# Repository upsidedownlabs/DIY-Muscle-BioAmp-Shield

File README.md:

# Muscle BioAmp Shield

[-white)](https://store.upsidedownlabs.tech/product/muscle-bioamp-shield-v0-3/)

Muscle BioAmp Shield is an all-in-one Arduino Uno ElectroMyography (EMG) shield for learning neuroscience with ease. It is a DIY Electrophysiology/NeuroScience shield inspired from Back Yard Brains (BYB) Muscle Spiker shield and provides similar features like hobby servo output, user buttons, LED Bar, Audio output, and battery input. It is perfect for beginners as they can easily stack it on top of Arduino Uno to record, visualize and listen to their muscle signals to make amazing projects in the domain of Human-Computer Interface (HCI).

## Features & Specifications

Muscle BioAmp Shield comes with various plug-and-play options so you can connect hundreds of extension boards like OLED screens, character displays, accelerometers, and servo controllers to name just a few using the STEMMA I2C interface. You also get STEMMA digital and STEMMA analog ports. On STEMMA analog port you can connect additional [BioAmp EXG Pill](https://github.com/upsidedownlabs/BioAmp-EXG-Pill) or any other sensor with analog output. On STEMMA digital port you can connect any digital sensor or actuator of your choice.

## Assembly
You can get your own Muscle BioAmp Shield bag of parts from [our store](https://store.upsidedownlabs.tech/product/muscle-bioamp-shield-v0-3/) or [Tindie](www.tindie.com/products/upsidedownlabs/muscle-bioamp-shield-v03-arduino-shield-for-emg/) and for assembling your shield you can take a look at [this interactive BOM](https://upsidedownlabs.github.io/DIY-Muscle-BioAmp-Shield/ibom.html) or the step by step guide below. 

| Step 1 - Bare board | Step 2 - 1M Resistors | Step 3 - 330R Resistors| 
| :----: | :----: | :----: |
| |||

| Step 4 - 10K Resistors | Step 5 - 22K Resistors | Step 6 - 1K Resistors| 
| :----: | :----: | :----: |
| |||

| Step 7 - 220K Resistors | Step 8 - 1nF Capacitors | Step 9 - 100nF Capacitors| 
| :----: | :----: | :----: |
| |||

| Step 10 - 100pF Capacitors | Step 11 - Servo Header Pin | Step 12 - Buttons| 
| :----: | :----: | :----: |
| |||

| Step 13 - Optoisolator | Step 14 - Angled JST Connectors | Step 15 - Straight JST Connectors| 
| :----: | :----: | :----: |
| |||

| Step 16 - IC Socket | Step 17 - IC | Step 18 - LEDs| 
| :----: | :----: | :----: |
| |||

| Step 19 - 3.5mm Headphone Jack | Step 20 - 2.2uF Capacitor | Step 21 - 1uF Capacitor| 
| :----: | :----: | :----: |
| |||

| Step 22 - 470uF Capacitors | Step 23 - Shield Header Pins | Step 24 - Shield Ready| 
| :----: | :----: | :----: |
| |||

## What's in the kit

Muscle BioAmp Shield comes in two variants: Pre-Assembled and DIY (Do-It-Yourself). You can order any of the two variants as per your requirement.

## Hardware

Muscle BioAmp Shield has been created using KiCad and all the design files can be found under [hardware](hardware/) folder, including [Interactive BOM](https://upsidedownlabs.github.io/DIY-Muscle-BioAmp-Shield/ibom.html) file. Images below shows a quick overview of the hardware design.

| PCB front | PCB back |
| :-------: | :--------: |
|  |  |

## License

#### Hardware
CERN Open Hardware License Version 2 - Strongly Reciprocal ([CERN-OHL-S-2.0](https://spdx.org/licenses/CERN-OHL-S-2.0.html)).

#### Software
MIT open source [license](http://opensource.org/licenses/MIT).

#### Documentation:
<br />This work is licensed under a <a rel="license" href="http://creativecommons.org/licenses/by/4.0/">Creative Commons Attribution 4.0 International License</a>.

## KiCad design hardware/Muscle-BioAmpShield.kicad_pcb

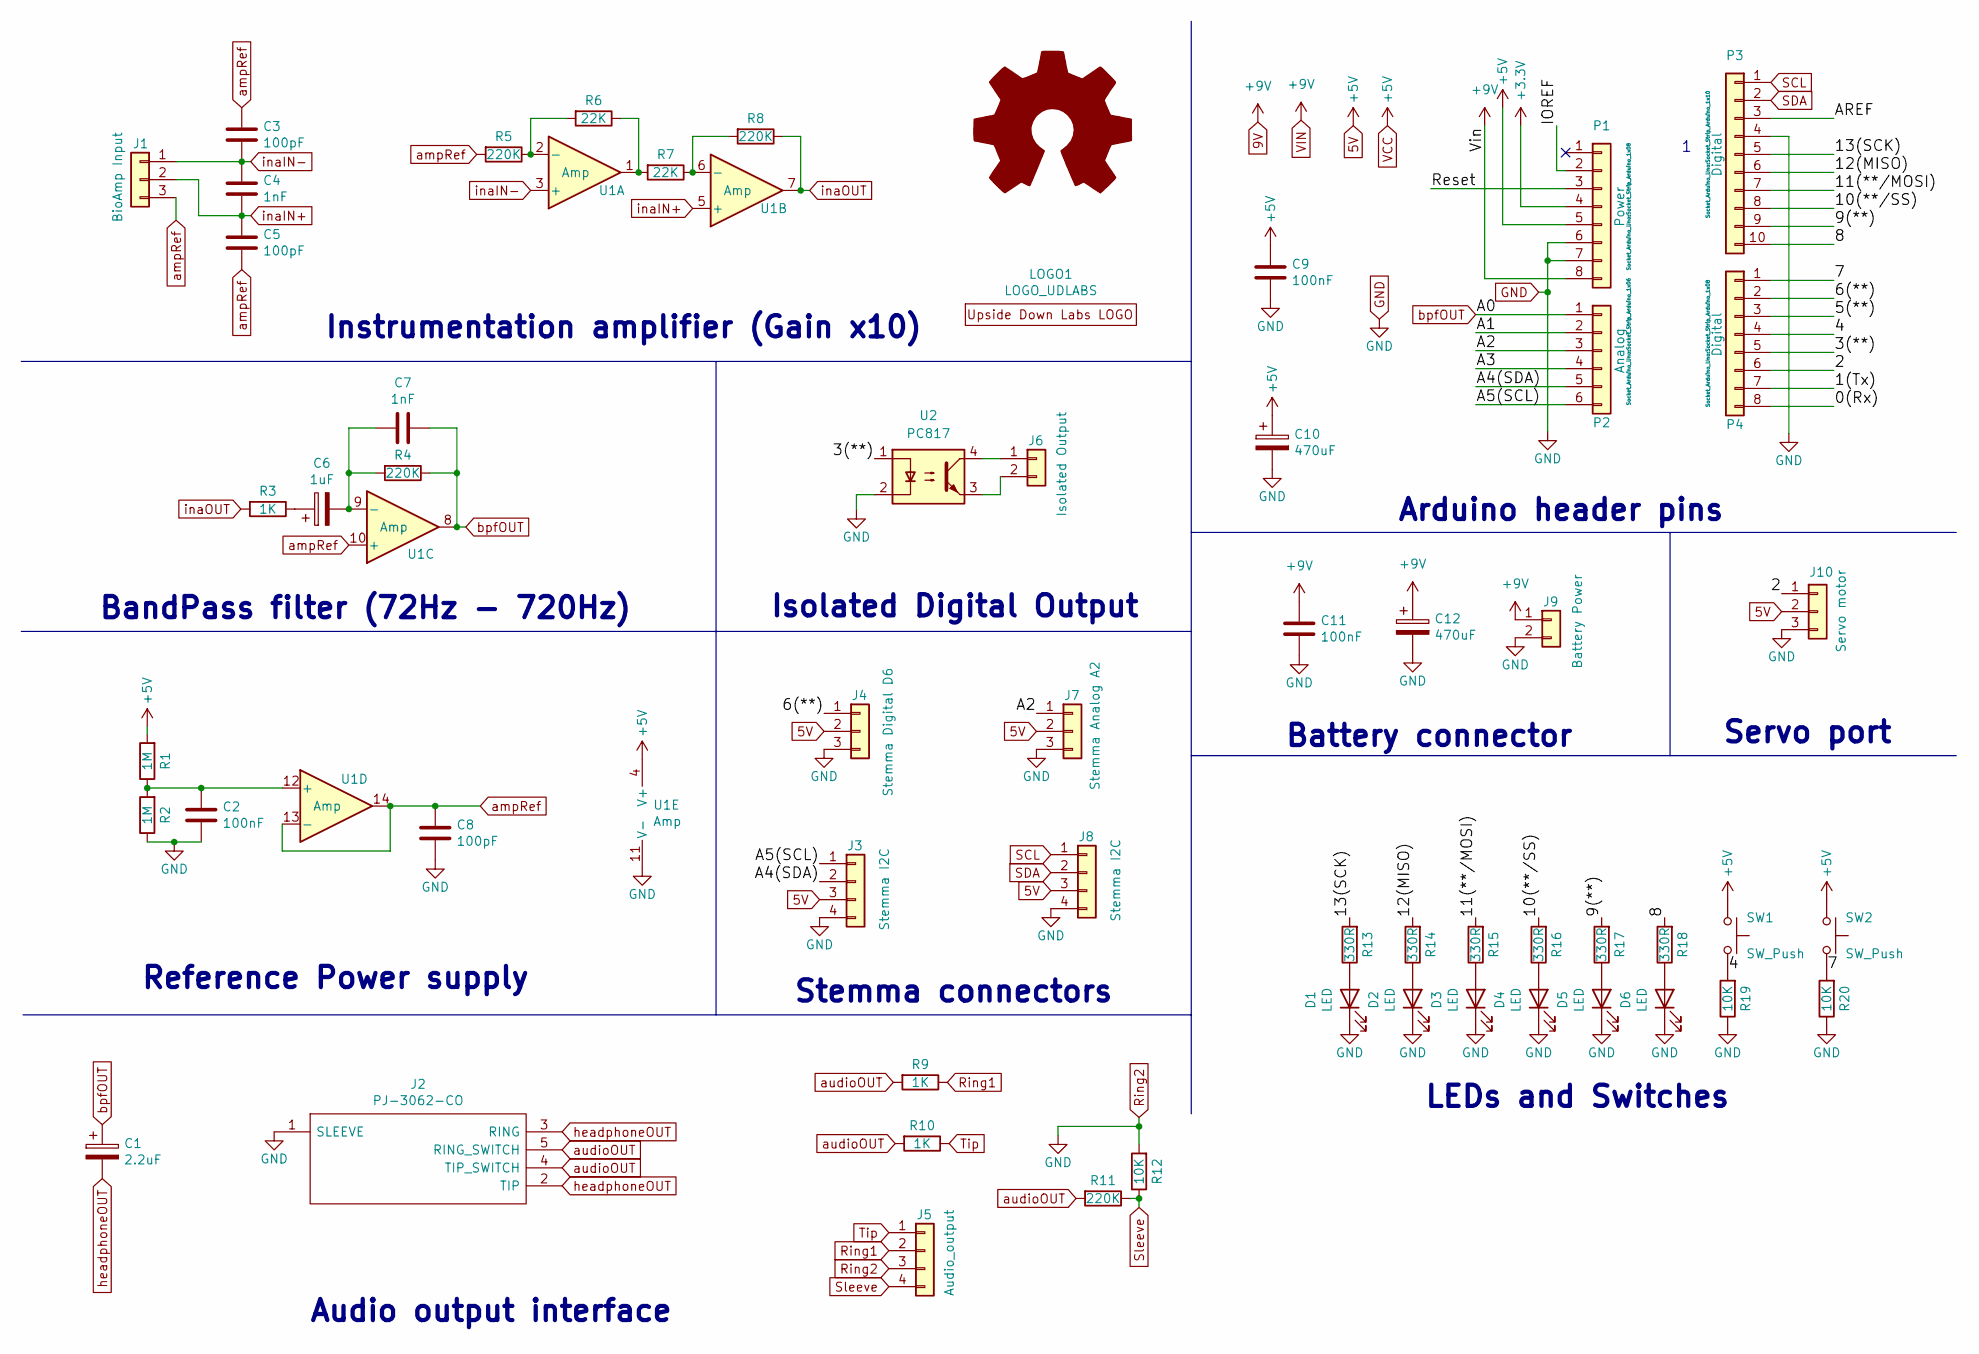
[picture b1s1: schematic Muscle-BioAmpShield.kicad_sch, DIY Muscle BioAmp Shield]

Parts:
C1: 2.2uF; CP_Radial_D5.0mm_P2.50mm
C2, C9, C11: 100nF; C_Disc_D3.8mm_W2.6mm_P2.50mm
C3, C5, C8: 100pF; C_Disc_D3.8mm_W2.6mm_P2.50mm
C4, C7: 1nF; C_Disc_D3.8mm_W2.6mm_P2.50mm
C6: 1uF; CP_Radial_D5.0mm_P2.50mm
C10, C12: 470uF; CP_Radial_D5.0mm_P2.50mm
D1, D2, D3, D4, D5, D6: LED; LED_D5.0mm
J1: BioAmp Input; JST_PH_S3B-PH-K_1x03_P2.00mm_Horizontal
J2: PJ-3062-CO; PJ3062CO; Manufacturer_Part_Number PJ-3062-CO
J3: Stemma I2C; JST_PH_B4B-PH-K_1x04_P2.00mm_Vertical
J4: Stemma Digital D6; JST_PH_B3B-PH-K_1x03_P2.00mm_Vertical
J5: Audio_output; JST_PH_S4B-PH-K_1x04_P2.00mm_Horizontal
J6: Isolated Output; JST_PH_B2B-PH-K_1x02_P2.00mm_Vertical
J7: Stemma Analog A2; JST_PH_B3B-PH-K_1x03_P2.00mm_Vertical
J8: Stemma I2C; JST_PH_S4B-PH-K_1x04_P2.00mm_Horizontal
J9: Battery Power; JST_PH_S2B-PH-K_1x02_P2.00mm_Horizontal
J10: Servo motor; PinHeader_1x03_P2.54mm_Vertical
LOGO1: LOGO_UDLABS; upsidedownlabsLOGO_41x34
P1: Power; Socket_Strip_Arduino_1x08
P2: Analog; Socket_Strip_Arduino_1x06
P3: Digital; Socket_Strip_Arduino_1x10
P4: Digital; Socket_Strip_Arduino_1x08
R1, R2: 1M; R_Axial_DIN0207_L6.3mm_D2.5mm_P7.62mm_Horizontal
R3, R9, R10: 1K; R_Axial_DIN0207_L6.3mm_D2.5mm_P7.62mm_Horizontal
R4, R5, R8, R11: 220K; R_Axial_DIN0207_L6.3mm_D2.5mm_P7.62mm_Horizontal
R6, R7: 22K; R_Axial_DIN0207_L6.3mm_D2.5mm_P7.62mm_Horizontal
R12, R19, R20: 10K; R_Axial_DIN0207_L6.3mm_D2.5mm_P7.62mm_Horizontal
R13, R14, R15, R16, R17, R18: 330R; R_Axial_DIN0207_L6.3mm_D2.5mm_P7.62mm_Horizontal
SW1, SW2: SW_Push; SW_PUSH_6mm_H5mm
U1: Amp; DIP-14_W7.62mm_Socket_LongPads
U2: PC817; DIP-4_W7.62mm

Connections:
5V: C9.2, C10.1, J3.3, J4.2, J7.2, J8.3, J10.2, P1.5, R1.2, SW1.1, SW2.1, U1.4 (V+)
9V: C11.2, C12.1, J9.1, P1.8
+3V3: P1.4
/0(Rx): P4.8
/1(Tx): P4.7
/2: J10.1, P4.6
/3(**): P4.5, U2.1
/4: P4.4, R19.2, SW1.2
/5(**): P4.3
/6(**): J4.1, P4.2
/7: P4.1, R20.2, SW2.2
/8: P3.10, R18.2
/9(**): P3.9, R17.2
/10(**/SS): P3.8, R16.2
/11(**/MOSI): P3.7, R15.2
/12(MISO): P3.6, R14.2
/13(SCK): P3.5, R13.2
/A1: P2.2
/A2: J7.1, P2.3
/A3: P2.4
/A4(SDA): J3.2, P2.5
/A5(SCL): J3.1, P2.6
/AREF: P3.3
/IOREF: P1.2
/Reset: P1.3
GND: C2.1, C8.1, C9.1, C10.2, C11.1, C12.2, D1.1 (K), D2.1 (K), D3.1 (K), D4.1 (K), D5.1 (K), D6.1 (K), J2.1 (SLEEVE), J3.4, J4.3, J5.3, J7.3, J8.4, J9.2, J10.3, P1.6, P1.7, P3.4, R2.1, R12.2, R19.1, R20.1, U1.11 (V-), U2.2
unnamed: C2.2, R1.1, R2.2, U1.12 (+)
unnamed: C6.1, R3.1
unnamed: C6.2, C7.1, R4.2, U1.9 (-)
unnamed: D1.2 (A), R13.1
unnamed: D2.2 (A), R14.1
unnamed: D3.2 (A), R15.1
unnamed: D4.2 (A), R16.1
unnamed: D5.2 (A), R17.1
unnamed: D6.2 (A), R18.1
unnamed: J6.1, U2.4
unnamed: J6.2, U2.3
unnamed: R5.1, R6.2, U1.2 (-)
unnamed: R6.1, R7.2, U1.1
unnamed: R7.1, R8.2, U1.6 (-)
Ring1: J5.2, R9.1
SCL: J8.1, P3.1
SDA: J8.2, P3.2
Sleeve: J5.4, R11.1, R12.1
Tip: J5.1, R10.1
ampRef: C3.2, C5.1, C8.2, J1.3, R5.2, U1.10 (+), U1.13 (-), U1.14
audioOUT: J2.4 (TIP_SWITCH), J2.5 (RING_SWITCH), R9.2, R10.2, R11.2
bpfOUT: C1.1, C7.2, P2.1, R4.1, U1.8
headphoneOUT: C1.2, J2.2 (TIP), J2.3 (RING)
inaIN+: C4.1, C5.2, J1.2, U1.5 (+)
inaIN-: C3.1, C4.2, J1.1, U1.3 (+)
inaOUT: R3.2, R8.1, U1.7

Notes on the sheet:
BandPass filter (72Hz - 720Hz)
Stemma connectors
Arduino header pins
Battery connector
Reference Power supply
Isolated Digital Output
Servo port
Audio output interface
LEDs and Switches
Instrumentation amplifier (Gain x10)

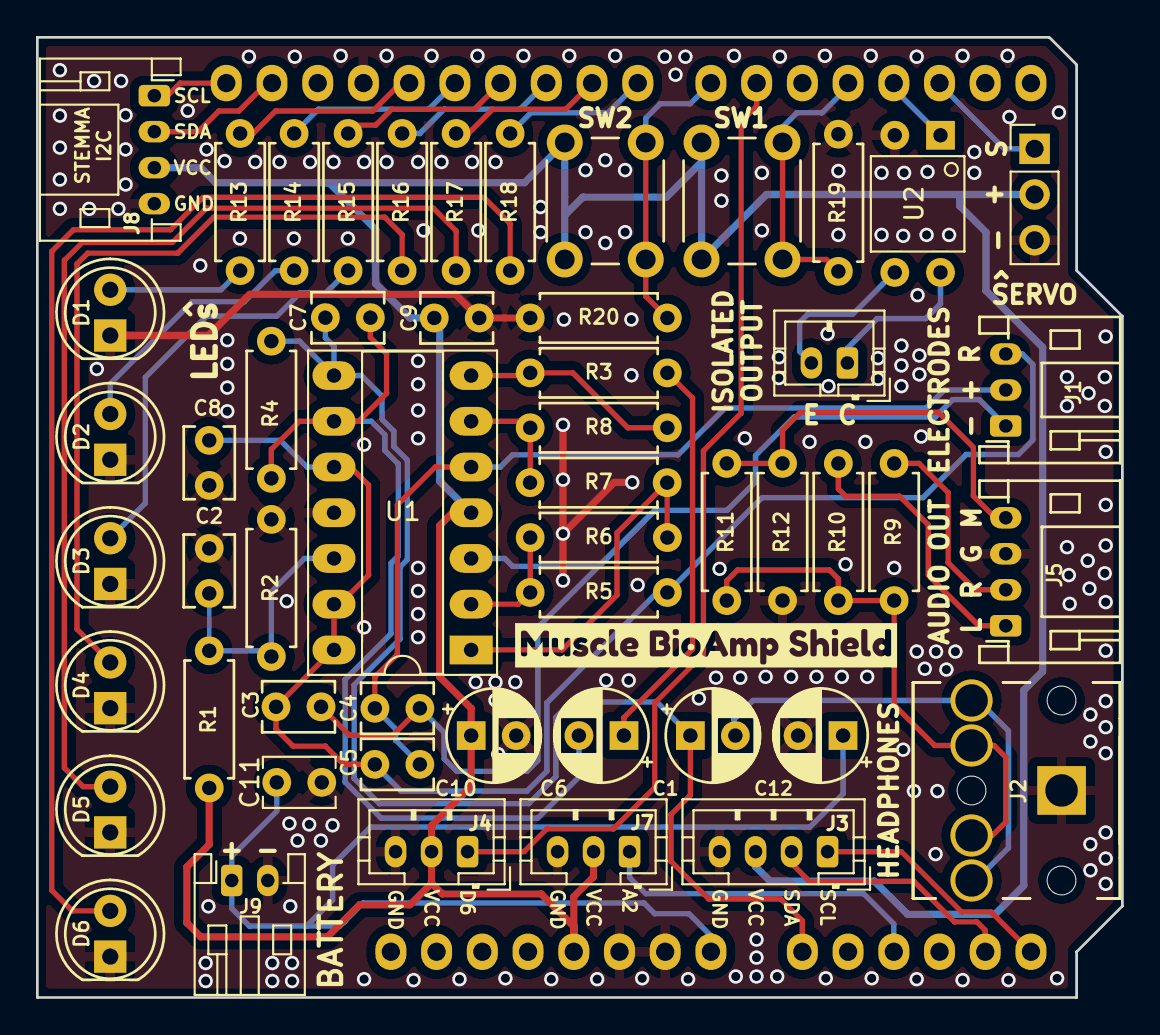
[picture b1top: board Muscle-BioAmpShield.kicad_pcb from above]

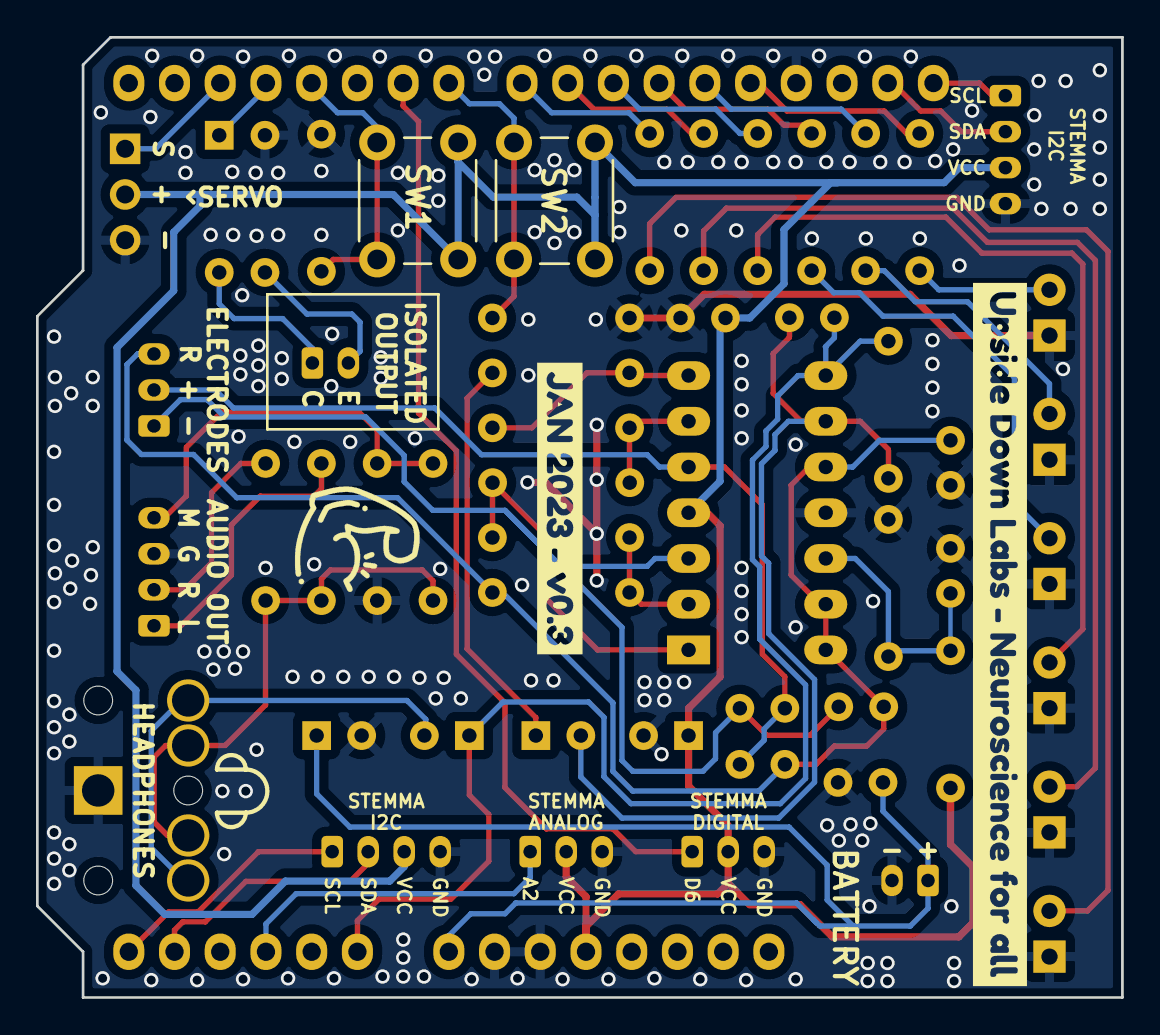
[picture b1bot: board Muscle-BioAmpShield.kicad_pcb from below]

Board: 2 copper layers, 60.3 x 53.3 mm, 59 parts (2 on the bottom side), 43 nets.

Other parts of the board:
kibuzzard-63B5E73F: G***; kibuzzard-63B5E73F
kibuzzard-63B67C69: G***; kibuzzard-63B67C69
kibuzzard-63B65023: G***; kibuzzard-63B65023

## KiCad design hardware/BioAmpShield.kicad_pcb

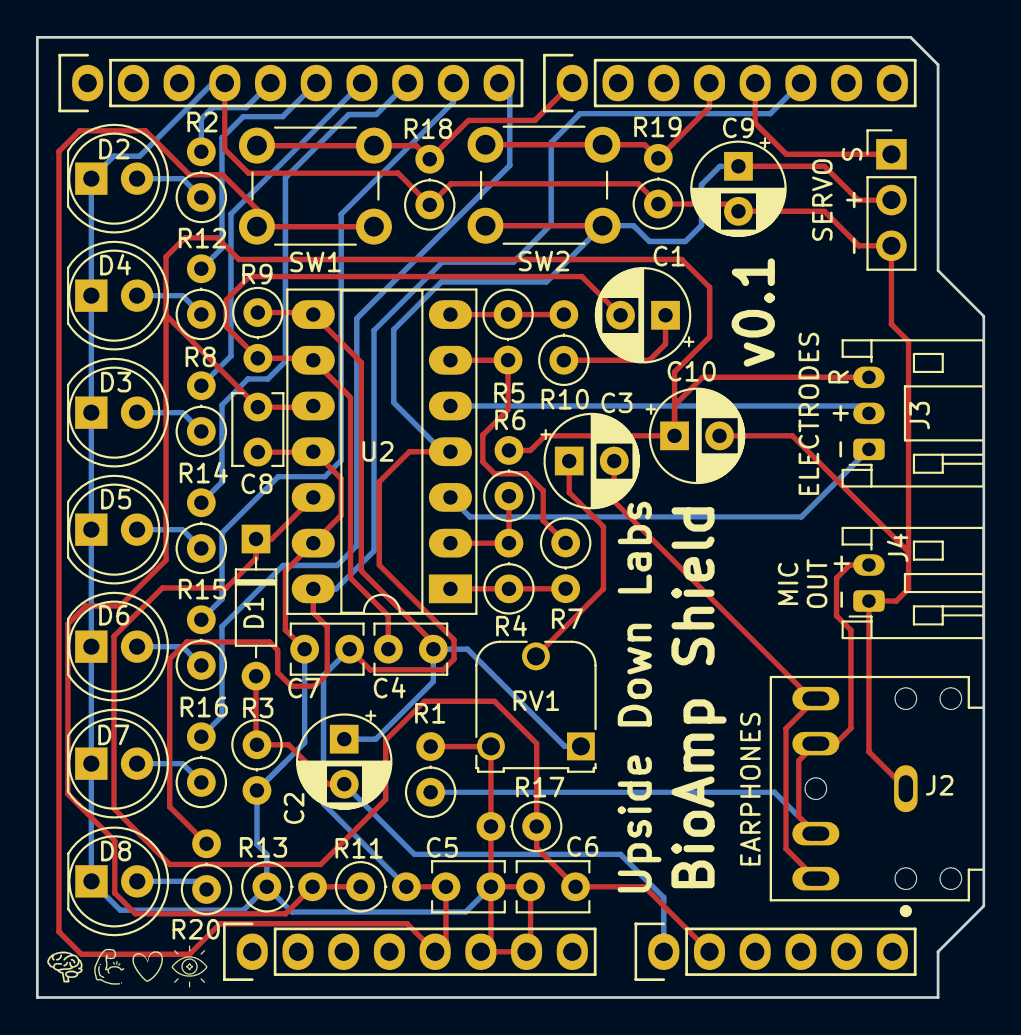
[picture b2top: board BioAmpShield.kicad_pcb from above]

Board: 2 copper layers, 52.6 x 53.3 mm, 50 parts (0 on the bottom side), 36 nets.

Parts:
C1: 47uF; CP_Radial_D5.0mm_P2.50mm
C2, C3, C9, C10: CP; CP_Radial_D5.0mm_P2.50mm
C4: 20nF; C_Disc_D3.8mm_W2.6mm_P2.50mm
C5: 100nF; C_Disc_D3.8mm_W2.6mm_P2.50mm
C6: 47nF; C_Disc_D3.8mm_W2.6mm_P2.50mm
C7, C8: 220nF; C_Disc_D3.8mm_W2.6mm_P2.50mm
D1: D; D_DO-35_SOD27_P7.62mm_Horizontal
D2, D3, D4, D5, D6, D7, D8: LED; LED_D5.0mm
J1: Conn_01x03; PinHeader_1x03_P2.54mm_Vertical
J2: SJ1-3525N; CUI_SJ1-3525N
J3: Conn_01x03; JST_PH_S3B-PH-K_1x03_P2.00mm_Horizontal
J4: Conn_01x02; JST_PH_S2B-PH-K_1x02_P2.00mm_Horizontal
P1: Power; Socket_Strip_Arduino_1x08
P2: Analog; Socket_Strip_Arduino_1x06
P3: Digital; Socket_Strip_Arduino_1x10
P4: Digital; Socket_Strip_Arduino_1x08
R1: 10k; R_Axial_DIN0207_L6.3mm_D2.5mm_P2.54mm_Vertical
R2, R4, R7, R8, R10, R11, R12, R13, R14, R15, R16, R20: 1K; R_Axial_DIN0207_L6.3mm_D2.5mm_P2.54mm_Vertical
R3: 100k; R_Axial_DIN0207_L6.3mm_D2.5mm_P2.54mm_Vertical
R5, R6: 10K; R_Axial_DIN0207_L6.3mm_D2.5mm_P2.54mm_Vertical
R9, R17, R18, R19: 1M; R_Axial_DIN0207_L6.3mm_D2.5mm_P2.54mm_Vertical
RV1: R_POT_Small; Potentiometer_Runtron_RM-065_Vertical
SW1, SW2: SW_Push; SW_PUSH_6mm_H5mm
U2: TL074; DIP-14_W7.62mm_Socket_LongPads

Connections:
+5V: C5.2, C7.1, C9.1, J1.2, P1.5, R11.2, SW1.1, SW2.1, U2.4
/3(**): J1.1, P4.5
/4: P4.4, R19.2, SW2.2
/7: P4.1, R18.2, SW1.2
/8: P3.10, R16.2
/9(**): P3.9, R15.2
/10(**/SS): P3.8, R14.2
/11(**/MOSI): P3.7, R8.2
/12(MISO): P3.6, R12.2
/13(SCK): P3.5, R2.2
/A4(SDA): P2.5, P3.2
/A5(SCL): P2.6, P3.1
GND: C5.1, C6.1, C7.2, C8.2, C9.2, C10.2, D2.1, D3.1, D4.1, D5.1, D6.1, D7.1, D8.1, J1.3, J2.1, J4.1, P1.6, P1.7, P3.4, R1.2, R3.2, R13.1, R17.2, R18.1, R19.1, RV1.3, U2.11, U2.13
IN+: J3.2, U2.5
IN-: J3.1, U2.3
unnamed: C1.1, R10.1
unnamed: C1.2, C4.2, R9.2, U2.9
unnamed: C2.1, C4.1, R9.1, RV1.1, U2.8
unnamed: C3.1, RV1.2
unnamed: D2.2, R2.1
unnamed: D3.2, R8.1
unnamed: D4.2, R12.1
unnamed: D5.2, R14.1
unnamed: D6.2, R15.1
unnamed: D7.2, R16.1
unnamed: D8.2, R20.1
unnamed: R4.1, R7.2, U2.1
unnamed: R4.2, R6.1, U2.2
unnamed: R5.2, R7.1, U2.6
ampRef: C8.1, C10.1, J3.3, R6.2, R11.1, R13.2, U2.10
analogOUT: C2.2, D1.2, P2.1, R3.1
audioOUT: C3.2, J2.2, J2.3
digitalOUT: P4.6, R20.2, U2.14
envelopOUT: C6.2, D1.1, P2.2, R17.1, U2.12
inaOUT: R5.1, R10.2, U2.7
micOUT: J2.10, J2.11, J4.2, R1.1

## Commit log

2022-03-09 Update licence
2022-03-09 Muscle BioAmp Shield v0.1b
2022-03-09 Muscle BioAmp Shield kicad files
2022-06-08 LED bar graph software
2022-06-08 Update information
2022-12-01 Update gitignore
2022-12-01 Add schematic
2022-12-01 Add envelope code
2022-12-01 Update hardware
2022-12-01 Add graphics
2022-12-26 Update final design
2023-01-02 Update v0.2 data
2023-01-02 Update v0.2 schematic
2023-01-02 Update v0.2 graphics
2023-01-02 v0.2 schematic PDF
2023-01-02 Fix Arduino code spelling
2023-02-13 Add v0.3 tilted render
2023-02-13 Add v0.3 renders
2023-02-14 Add v0.3 SVG graphics
2023-02-14 initial code example
2023-02-14 Update to v0.3 KiCad files
2023-02-14 Upload interactive BOM
2023-02-14 Add prefix DIY
2023-02-14 Update v0.3 schematic PNG
2023-02-14 Update img shields
    Updated all the important links for shield v0.3
2023-02-16 Update shield graphics
    Update shield v0.3 renders, svgs, text.
    Add detailed features and specifications.
2023-02-16 Update shield tilted render
2023-02-16 Update tilted render
2023-02-16 Update tilted renders
2023-02-17 Update Render files
2023-02-17 V0.3 graphics update (#1)
    * Update img shields
    Updated all the important links for shield v0.3
    * Update shield graphics
    Update shield v0.3 renders, svgs, text.
    Add detailed features and specifications.
    * Update shield tilted render
2023-02-24 Update Shield assembly guide
2023-02-27 Optimize shield renders
2023-02-27 Update Shield Assembly Guide (#2)
    * Update img shields
    Updated all the important links for shield v0.3
    * Update shield graphics
    Update shield v0.3 renders, svgs, text.
    Add detailed features and specifications.
    * Update shield tilted render
2023-05-06 Update SVG graphics
    Update the assembled shield SVG, shield with wires SVG.
2023-05-06 Fix SVG graphics (#3)
    * Update img shields
    Updated all the important links for shield v0.3
    * Update shield graphics
    Update shield v0.3 renders, svgs, text.
    Add detailed features and specifications.
    * Update shield tilted render
2023-05-25 minor filled zone update
2023-05-25 Add dimensions graphics
2023-06-22 Update BOM file and redirect index to docs site
2023-07-14 Update README.md
    Update interactive BOM link
2023-08-07 Update index.html
    Redirected to docs site
